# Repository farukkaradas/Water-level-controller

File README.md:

# Water-level-controller
Capacitance based DC water level controller with PWM

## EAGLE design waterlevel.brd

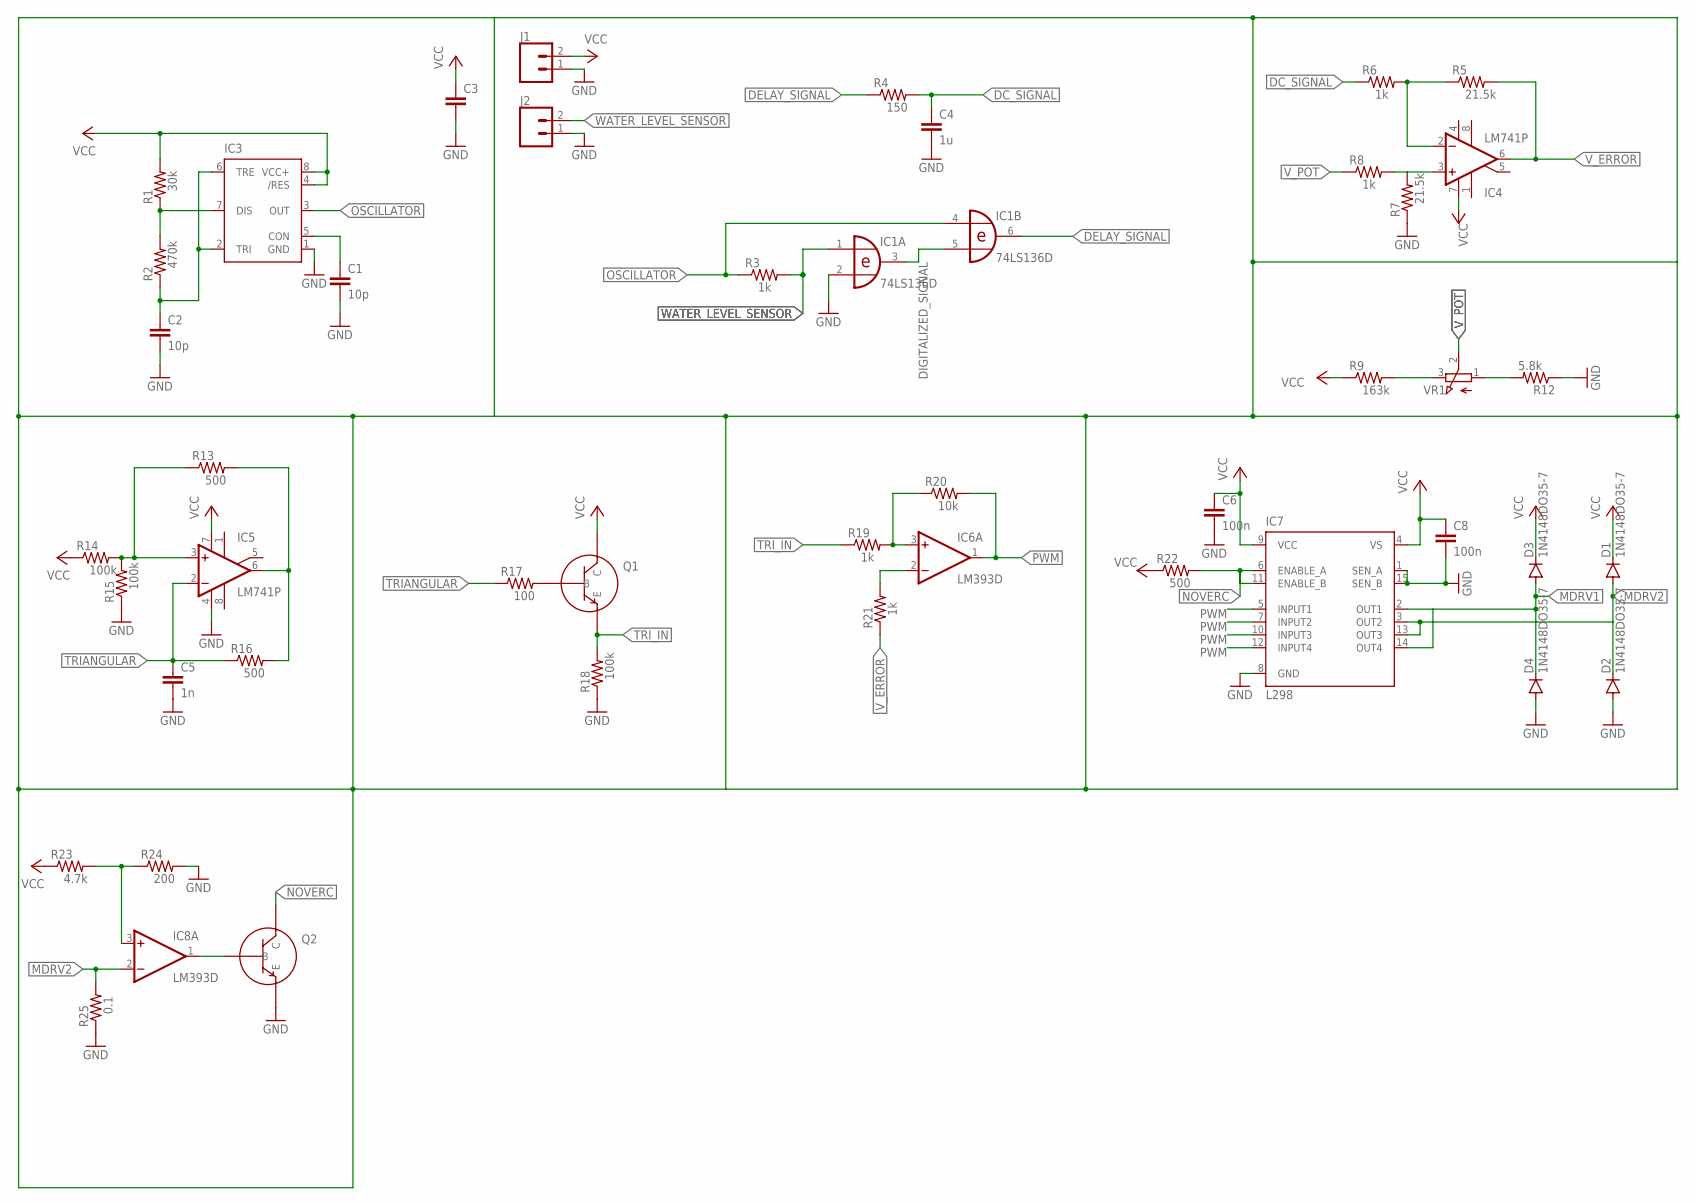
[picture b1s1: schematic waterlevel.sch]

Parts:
C1, C2: 10p; C0603
C3: C-EUC0603; C0603
C4: 1u; C0603
C5: 1n; C0603
C6, C8: 100n; C0603
D1, D2, D3, D4: 1N4148DO35-7; DO35-7
IC1: 74LS136D; DIL14
IC3: 555; SO08
IC4, IC5: LM741P; DIL08
IC6, IC8: LM393D; SO08
IC7: L298; MULTIWATT-15
J1, J2: CONN_022; 1X02
R1: 30k; R0603
R2: 470k; R0603
R3, R6, R8, R19, R21: 1k; R0603
R4: 150; R0603
R5, R7: 21.5k; R0603
R9: 163k; R0603
R12: 5.8k; R0603
R13, R16, R22: 500; R0603
R14, R15, R18: 100k; R0603
R17: 100; R0603
R20: 10k; R0603
R23: 4.7k; R0603
R24: 200; R0603
R25: 0.1; R0603
VR1: 10k; 3RP/1610N

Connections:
DC_SIGNAL: C4.1, R4.2, R6.1
DELAY_SIGNAL: IC1.6 (O), R4.1
DIGITALIZED_SIGNAL: IC1.3 (O), IC1.5 (I1)
GND: C1.2, C2.2, C3.2, C4.2, C5.2, C6.2, C8.2, D2.A, D4.A, IC1.2 (I1), IC1.7 (GND), IC3.1 (GND), IC5.4 (V-), IC7.1 (SEN_A), IC7.8 (GND), IC7.15 (SEN_B), J1.1, J2.1, R7.1, R12.1, R15.1, R18.1, R24.2, R25.1
MDRV1: D3.A, D4.C, IC7.2 (OUT1), IC7.14 (OUT4)
MDRV2: D1.A, D2.C, IC7.3 (OUT2), IC7.13 (OUT3)
unnamed: IC3.7 (DIS), R1.1, R2.2
unnamed: R9.2, VR1.3 (E)
unnamed: C1.1, IC3.5 (CON)
unnamed: C2.1, IC3.2 (TRI), IC3.6 (TRE), R2.1
unnamed: IC4.2 (-IN), R5.1, R6.2
unnamed: IC4.3 (+IN), R7.2, R8.2
unnamed: IC5.6 (OUT), R13.2, R16.2
unnamed: IC5.3 (+IN), R13.1, R14.2, R15.2
unnamed: IC6.3 (+IN), R19.2, R20.1
unnamed: IC8.3 (+IN), R23.2, R24.1
unnamed: IC6.2 (-IN), R21.2
unnamed: IC8.2 (-IN), R25.2
NOVERC: IC7.6 (ENABLE_A), IC7.11 (ENABLE_B), R22.2
OSCILLATOR: IC1.4 (I0), IC3.3 (OUT), R3.1
PWM: IC6.1 (OUT), IC7.5 (INPUT1), IC7.7 (INPUT2), IC7.10 (INPUT3), IC7.12 (INPUT4), R20.2
TRIANGULAR: C5.1, IC5.2 (-IN), R16.1, R17.1
TRI_IN: R18.2, R19.1
V+: IC6.8 (V+), IC8.8 (V+)
V-: IC4.4 (V-), IC6.4 (V-), IC8.4 (V-)
VCC: C3.1, C6.1, C8.1, D1.C, D3.C, IC1.14 (VCC), IC3.4 (/RES), IC3.8 (VCC+), IC4.7 (V+), IC5.7 (V+), IC7.4 (VS), IC7.9 (VCC), J1.2, R1.2, R9.1, R14.1, R22.1, R23.1
V_ERROR: IC4.6 (OUT), R5.2, R21.1
V_POT: R8.1, R12.2, VR1.1 (A)
WATER_LEVEL_SENSOR: IC1.1 (I0), J2.2, R3.2

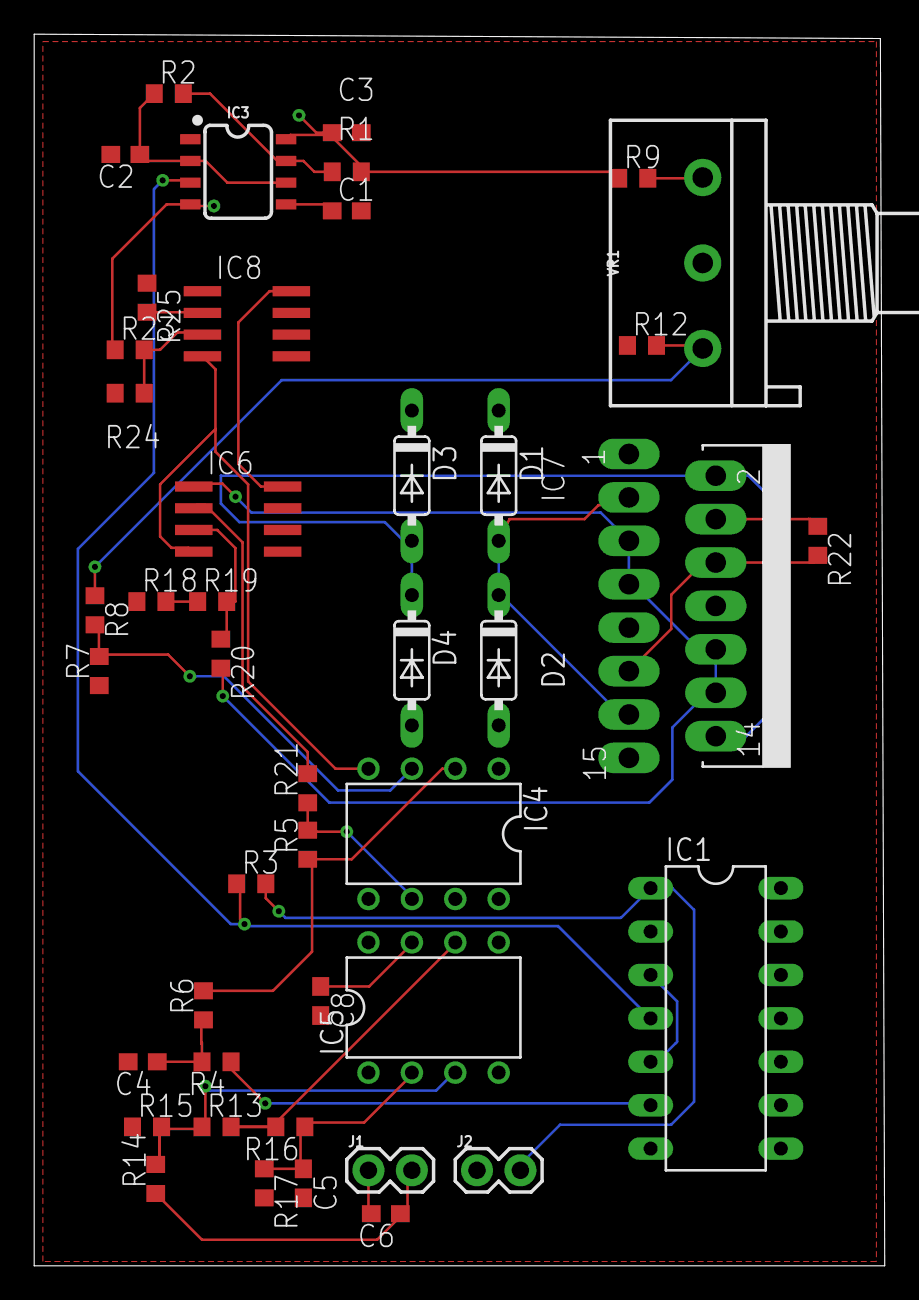
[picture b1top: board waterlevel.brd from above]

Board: 2 copper layers, 49.8 x 72.1 mm, 44 parts (0 on the bottom side), 29 nets.

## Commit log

2020-09-04 final report added
2020-09-04 name change
2020-09-22 minor changes

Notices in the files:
parts and their libraries:
SparkFun-IC-Special-Function: Licensing: Creative Commons ShareAlike 4.0 International - https://creativecommons.org/licenses/by-sa/4.0
